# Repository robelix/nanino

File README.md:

nanino rlx
==========

my variant of the nanino - a DIY friendly arduino clone

* pin-compatible with arduino shields
* DIY friendly single sided PCB
* FTDI connector
* prototyping area

based on nanoino by Johan von Konow  
http://vonkonow.com/wordpress/2012/10/nanino-the-diy-friendly-arduino/

License: [Creative Commons BY-NC-SA 3.0](http://creativecommons.org/licenses/by-nc-sa/3.0/)

## Changes in Version 1.1:
* Rx/Tx of FTDI corrected
* bigger solder pads

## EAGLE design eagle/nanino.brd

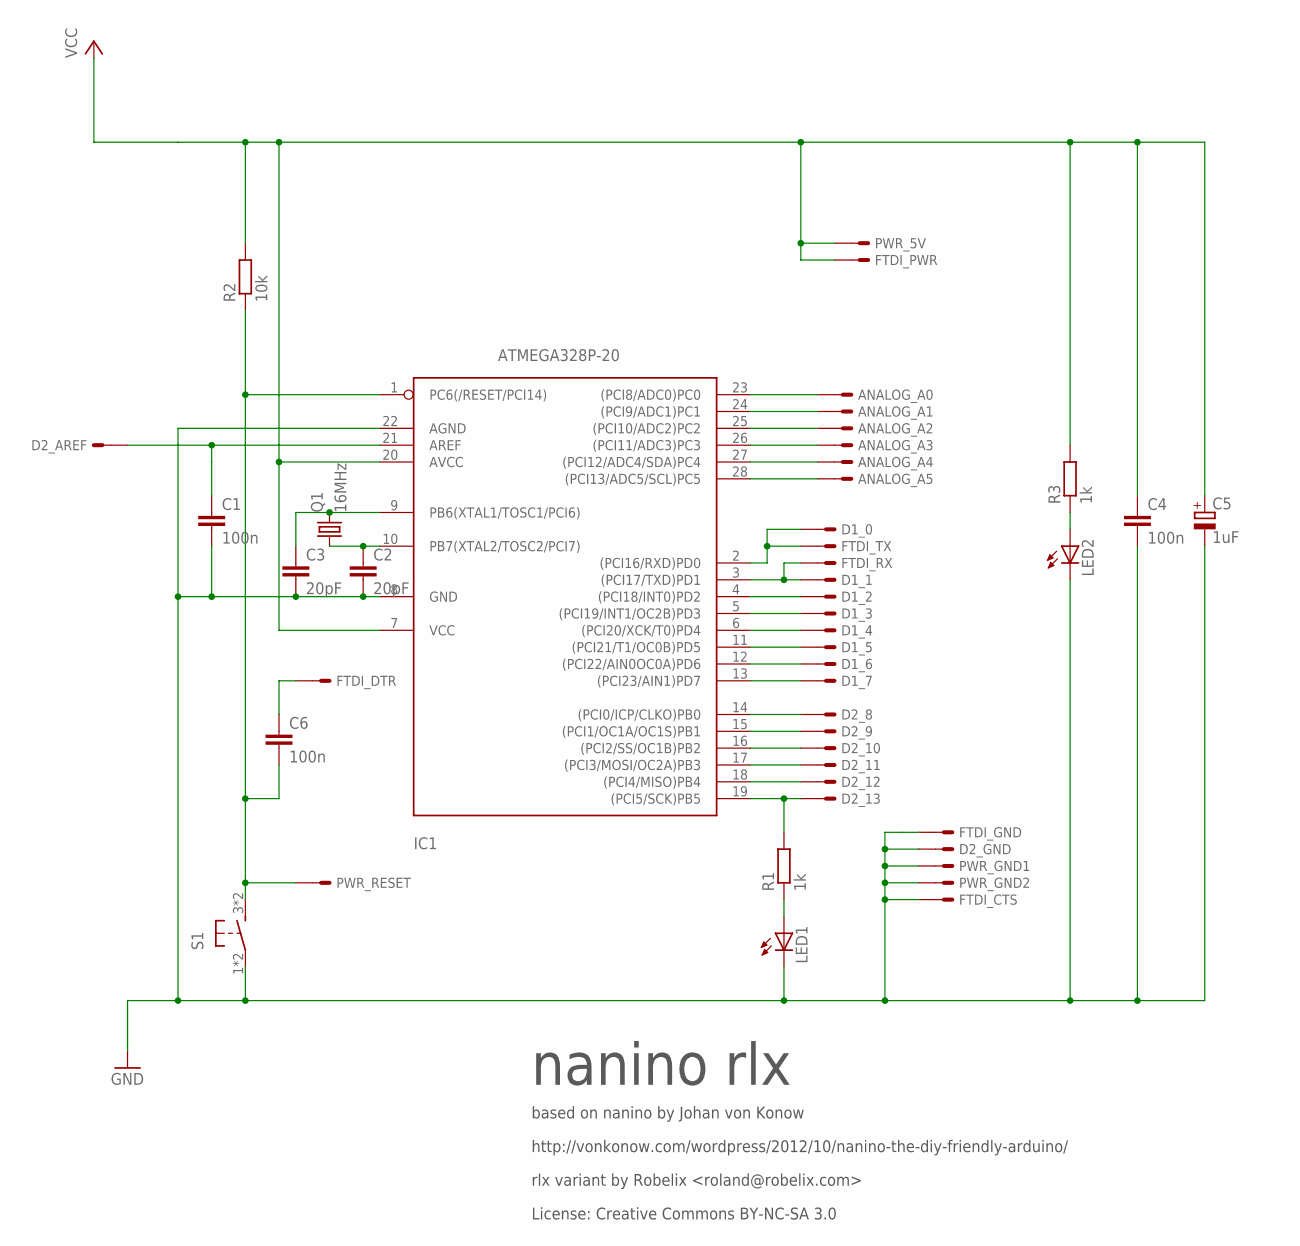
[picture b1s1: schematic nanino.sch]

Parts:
ANALOG_: PINS_ARDUINO_ANALOG1; 6PIN
C1, C4: 100n; C025-025X050
C2, C3: 20pF; C025-025X050
C5: 1uF; E2,5-5-L-12
C6: 100n; C050-025X075
D1_: PINS_ARDUINO_DIGITAL1; 8PIN
D2_: PINS_ARDUINO_DIGITAL2; 8PIN
FTDI_: PINS_FTDI1; 6PIN
IC1: ATMEGA328P-20; DIL28-3
LED1, LED2: LED3MM
PWR_: PINS_ARDUINO_PWR1; 6PIN
Q1: 16MHz; HC49U-V
R1, R3: 1k; 0207/10
R2: 10k; 0207/10
S1: TASTER4.3MM; TASTER6X6

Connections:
GND: C1.2, C2.2, C3.2, C4.2, C5.-, D2_.7, FTDI_.1, FTDI_.2, IC1.8 (GND), IC1.22 (AGND), LED1.K (C), LED2.K (C), PWR_.4, PWR_.5, S1.1, S1.2 (1)
unnamed: D1_.1, FTDI_.4, IC1.2 ((PCI16/RXD)PD0)
unnamed: D1_.2, FTDI_.5, IC1.3 ((PCI17/TXD)PD1)
unnamed: D1_.3, IC1.4 ((PCI18/INT0)PD2)
unnamed: D1_.4, IC1.5 ((PCI19/INT1/OC2B)PD3)
unnamed: D1_.5, IC1.6 ((PCI20/XCK/T0)PD4)
unnamed: D1_.6, IC1.11 ((PCI21/T1/OC0B)PD5)
unnamed: D1_.7, IC1.12 ((PCI22/AIN0OC0A)PD6)
unnamed: D1_.8, IC1.13 ((PCI23/AIN1)PD7)
unnamed: D2_.1, IC1.14 ((PCI0/ICP/CLKO)PB0)
unnamed: D2_.2, IC1.15 ((PCI1/OC1A/OC1S)PB1)
unnamed: D2_.3, IC1.16 ((PCI2/SS/OC1B)PB2)
unnamed: D2_.4, IC1.17 ((PCI3/MOSI/OC2A)PB3)
unnamed: D2_.5, IC1.18 ((PCI4/MISO)PB4)
unnamed: D2_.6, IC1.19 ((PCI5/SCK)PB5), R1.2
unnamed: LED1.A, R1.1
unnamed: ANALOG_.6, IC1.23 ((PCI8/ADC0)PC0)
unnamed: ANALOG_.5, IC1.24 ((PCI9/ADC1)PC1)
unnamed: ANALOG_.4, IC1.25 ((PCI10/ADC2)PC2)
unnamed: ANALOG_.3, IC1.26 ((PCI11/ADC3)PC3)
unnamed: ANALOG_.2, IC1.27 ((PCI12/ADC4/SDA)PC4)
unnamed: ANALOG_.1, IC1.28 ((PCI13/ADC5/SCL)PC5)
unnamed: C6.2, IC1.1 (PC6(/RESET/PCI14)), PWR_.1, R2.1, S1.3, S1.4 (3)
unnamed: LED2.A, R3.1
unnamed: C1.1, D2_.8, IC1.21 (AREF)
unnamed: C3.1, IC1.9 (PB6(XTAL1/TOSC1/PCI6)), Q1.2
unnamed: C2.1, IC1.10 (PB7(XTAL2/TOSC2/PCI7)), Q1.1
unnamed: C6.1, FTDI_.6
VCC: C4.1, C5.+, FTDI_.3, IC1.7 (VCC), IC1.20 (AVCC), PWR_.3, R2.2, R3.2

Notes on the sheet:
nanino rlx
based on nanino by Johan von Konow
http://vonkonow.com/wordpress/2012/10/nanino-the-diy-friendly-arduino/
rlx variant by Robelix <roland@robelix.com>
License: Creative Commons BY-NC-SA 3.0

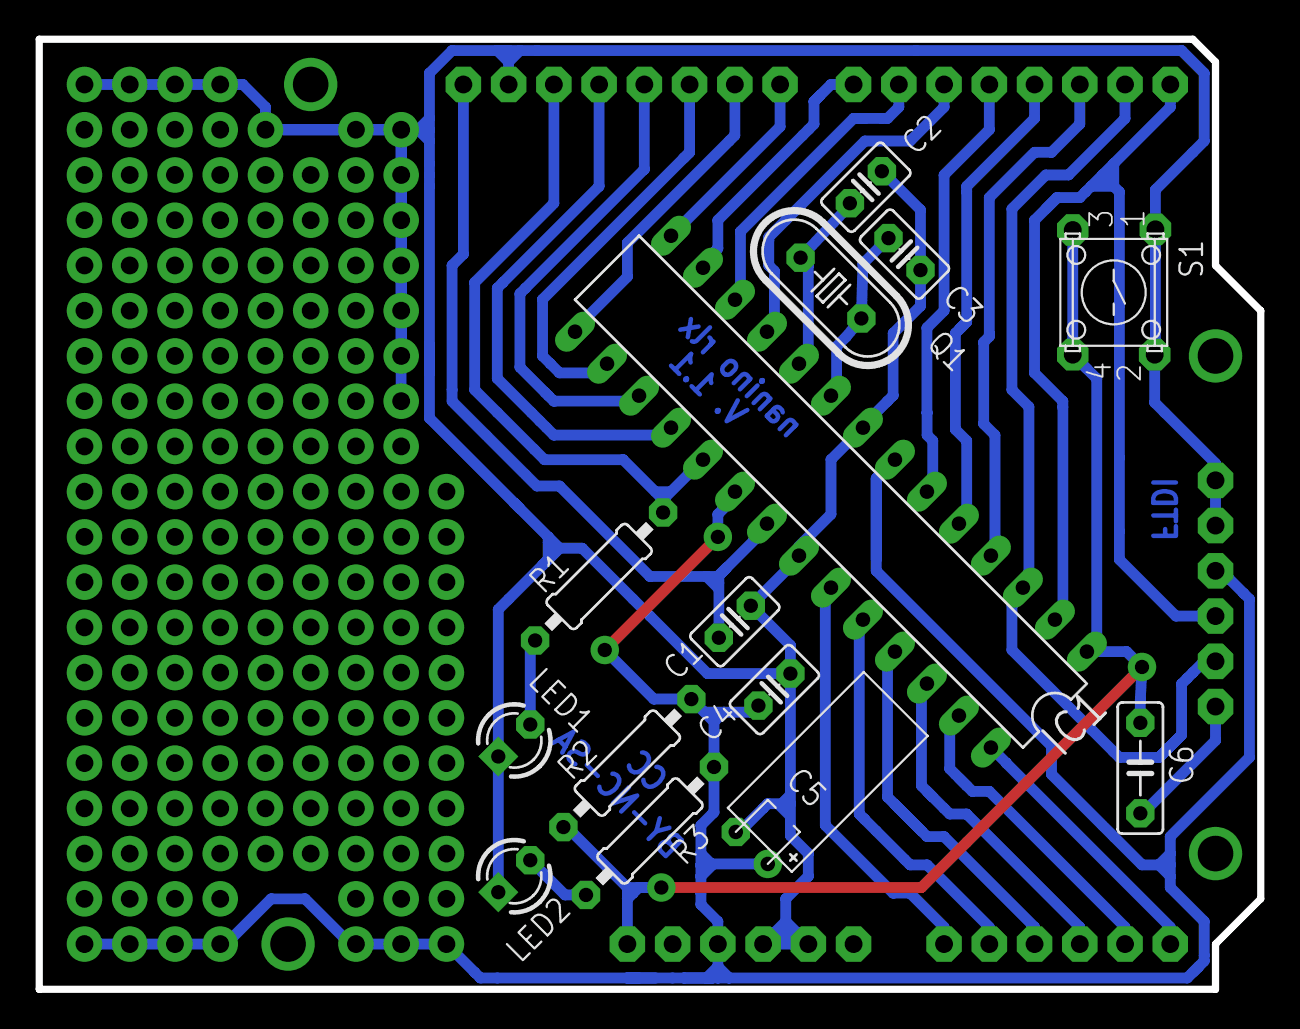
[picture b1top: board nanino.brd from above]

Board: 2 copper layers, 68.6 x 53.3 mm, 19 parts (0 on the bottom side), 29 nets.

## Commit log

2013-02-09 initial upload
2013-02-09 pdfs and images added
2013-02-09 images added to readme
2013-02-15 improved routing
2013-03-12 Version 1.1 - FTDI Rx/Tx corrected, bigger solder pads
2013-07-22 Power was connected to 3.3V Pin, not to 5V
2013-07-22 5V power was connected to 3.3V Pin
